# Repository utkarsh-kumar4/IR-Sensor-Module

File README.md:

<h1>🔦 IR Sensor Module</h1>

<p>
This project is a complete IR sensor module designed in <b>KiCad</b>. 
The design process included creating the schematic, drawing the PCB layout, 
and finally generating the 3D board view. The goal was to build a compact 
sensor module that can detect reflected infrared signals and provide a 
digital output.
</p>

<h2>📝 Project Steps</h2>
<p>
1. <b>Schematic Design:</b> The IR LED, photodiode, resistors, potentiometer, 
and LM358 op-amp were connected to form a comparator-based circuit.<br>
2. <b>PCB Layout:</b> The schematic was converted to PCB, components were placed, 
and tracks were routed to ensure proper signal flow.<br>
3. <b>3D Board View:</b> A 3D model of the PCB was generated to visualize 
component placement and final design.
</p>

<h2>🚀 Uses</h2>
<p>
- Obstacle detection for small robots 🤖<br>
- Line following sensors 🚗<br>
- Proximity sensing 📡<br>
- Basic automation projects ⚡
</p>

<h2>📷 Project Images</h2>
<h3>🔹 Schematic Design</h3>

<h3>🔹 PCB Layout</h3>

<h3>🔹 3D Board View</h3>

## Author 👤
[Utkarsh Kumar](https://github.com/utkarsh-kumar4) 👨🏻‍💻🎓

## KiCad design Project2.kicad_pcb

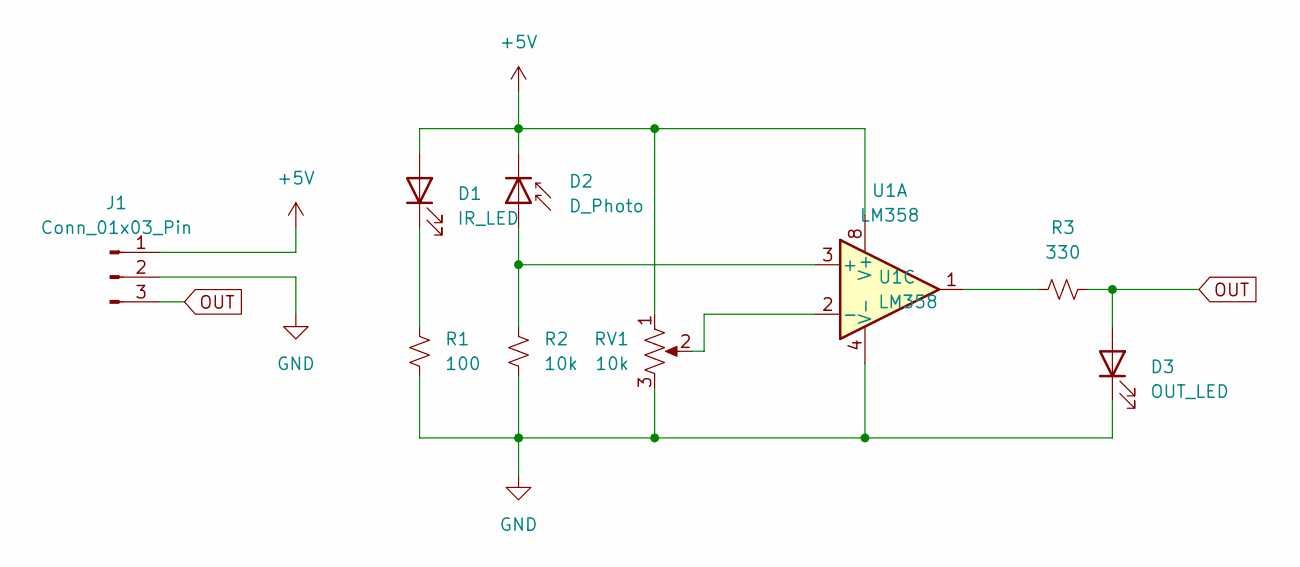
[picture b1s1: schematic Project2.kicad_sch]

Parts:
D1: IR_LED; LED_D5.0mm_Horizontal_O3.81mm_Z3.0mm
D2: D_Photo; LED_D5.0mm_Horizontal_O3.81mm_Z3.0mm
D3: OUT_LED; LED_1206_3216Metric
J1: Conn_01x03_Pin; PinHeader_1x03_P2.54mm_Horizontal
R1: 100; R_1206_3216Metric_Pad1.30x1.75mm_HandSolder
R2: 10k; R_1206_3216Metric_Pad1.30x1.75mm_HandSolder
R3: 330; R_1206_3216Metric_Pad1.30x1.75mm_HandSolder
RV1: 10k; Potentiometer_Bourns_3266Y_Vertical
U1: LM358; DIP-8_W7.62mm_SMDSocket_SmallPads

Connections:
+5V: D1.2 (A), D2.1 (K), J1.1, RV1.1, U1.8 (V+)
GND: D3.1 (K), J1.2, R1.2, R2.2, RV1.3, U1.4 (V-)
unnamed: D1.1 (K), R1.1
unnamed: D2.2 (A), R2.1, U1.3 (+)
unnamed: R3.1, U1.1
unnamed: RV1.2, U1.2 (-)
OUT: D3.2 (A), J1.3, R3.2

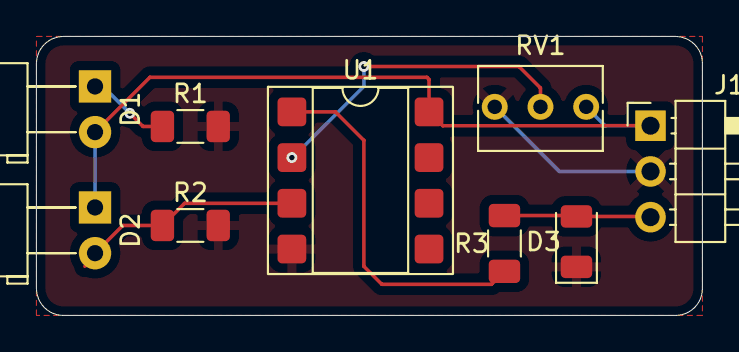
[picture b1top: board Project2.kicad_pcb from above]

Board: 2 copper layers, 37.0 x 15.5 mm, 9 parts (0 on the bottom side), 7 nets.

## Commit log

2025-09-29 Rename PCB 3D View.png to PCB 3D Board View.png
2025-09-29 Rename Schematic.png to Schematic View.png
2025-09-29 Rename PCB 3D Board View.png to 3D Board View.png
2025-09-29 Rename Schematic View.png to Schematic Design.png
